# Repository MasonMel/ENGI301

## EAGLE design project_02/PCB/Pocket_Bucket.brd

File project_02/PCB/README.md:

In this project, I implemented my project_01 design into a PCB. This involved creating my own library, schematic, and routing the board layout.

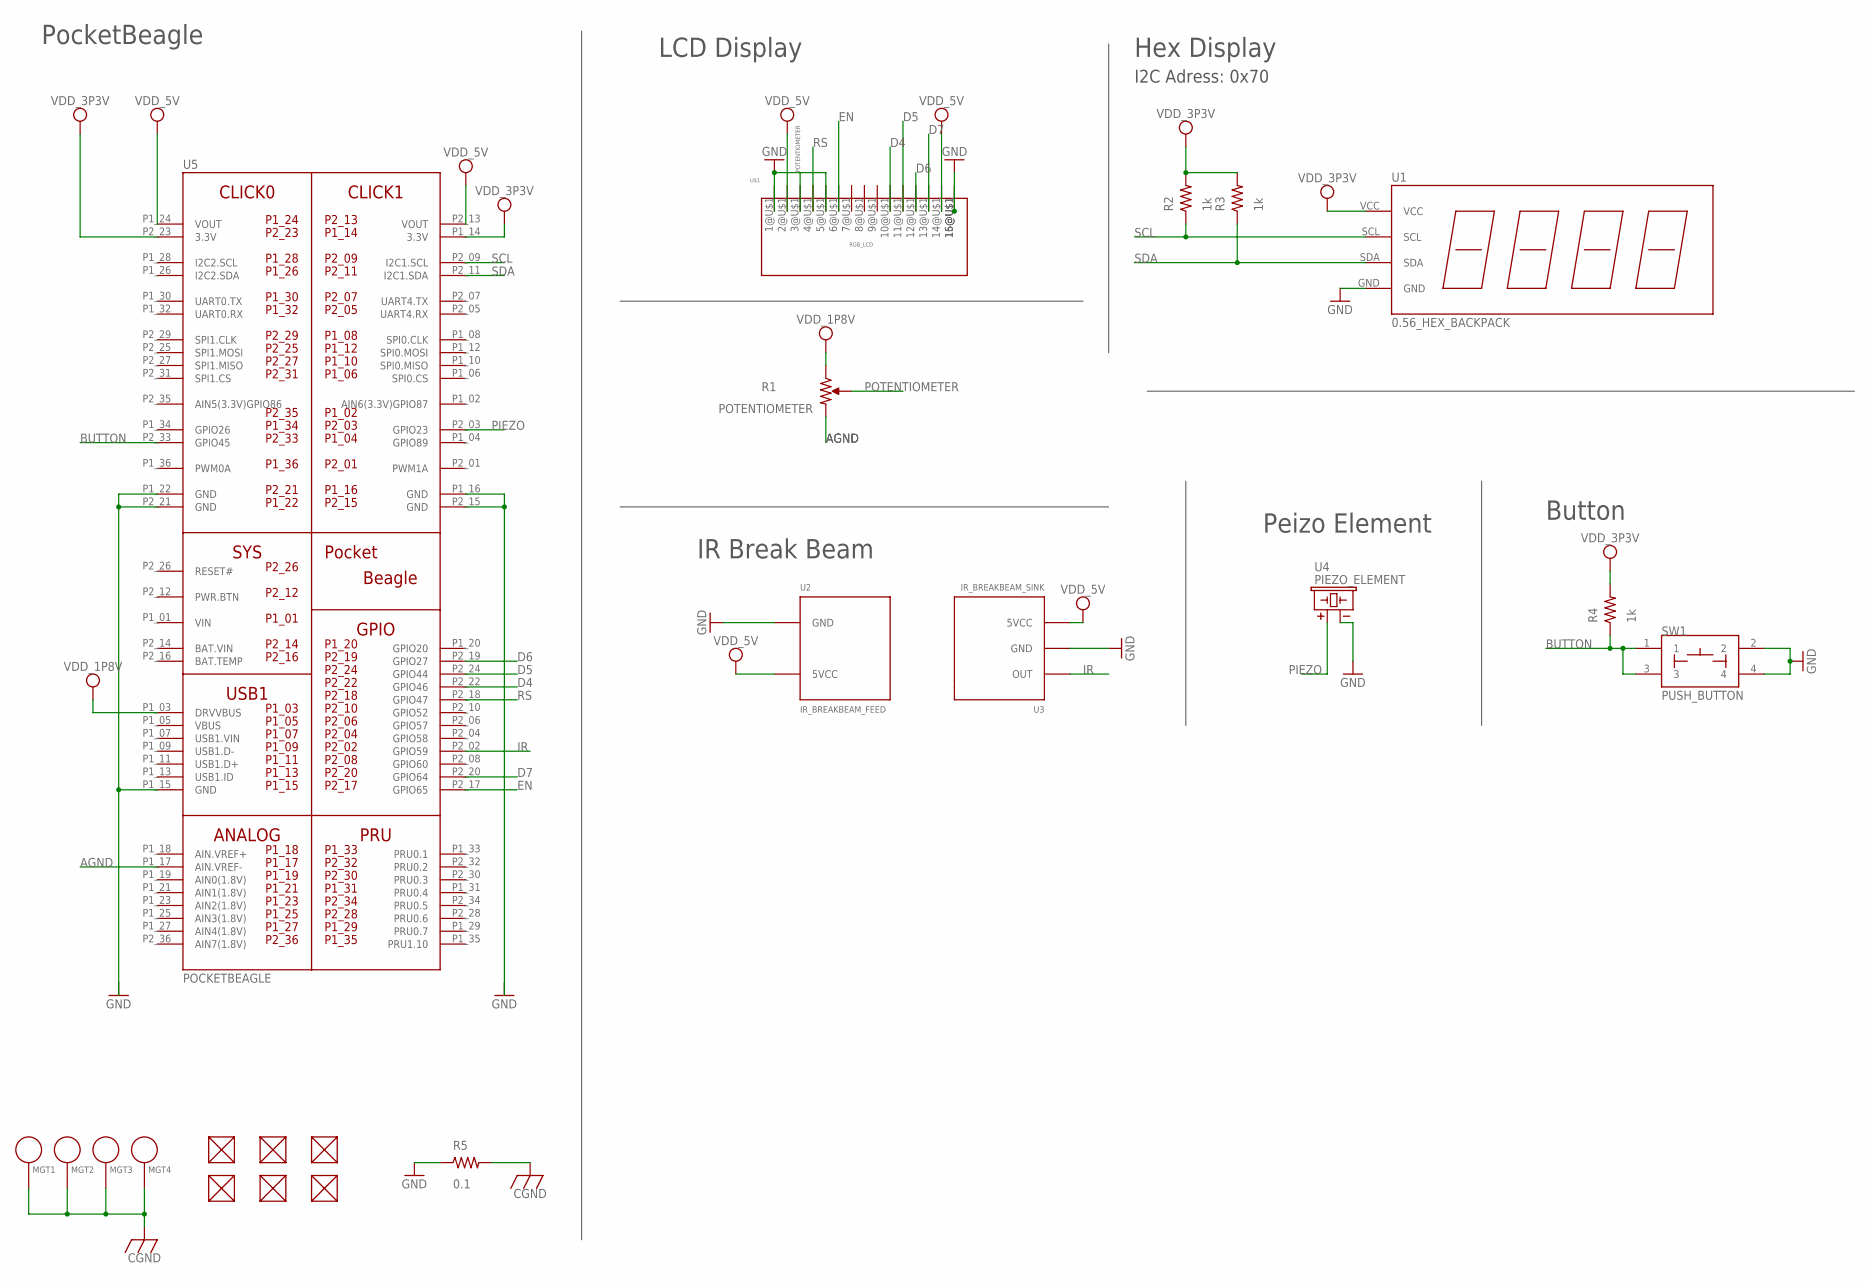
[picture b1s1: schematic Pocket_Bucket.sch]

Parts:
FUD1, FUD2, FUD3, FUD4, FUD5, FUD6: FIDUCIAL; FIDUCIAL_40MIL
MGT1, MGT2, MGT3, MGT4: MOUNTING_HOLE
R1: POTENTIOMETER; POT-PO90S
R2, R3, R4: 1k; R0603
R5: 0.1; R0805
SW1: PUSH_BUTTON; BUTTON_12.5MM
U1: 0.56_HEX_BACKPACK
U2: IR_BREAKBEAM_FEED
U3: IR_BREAKBEAM_SINK
U4: PIEZO_ELEMENT; BUZZER_6.5MM
U5: POCKETBEAGLE
U$1: RGB_LCD; ADAFRUIT_RGB_LCD

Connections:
AGND: R1.CW, U5.P1_15 (GND), U5.P1_17 (AIN.VREF-), U5.P1_22 (GND), U5.P2_21 (GND)
BAT.VIN: U5.P2_14 (BAT.VIN)
BUTTON: R4.1, SW1.1, SW1.3, U5.P2_33 (GPIO45)
CGND: MGT1.P$1, MGT2.P$1, MGT3.P$1, MGT4.P$1, R5.2
D4: U5.P2_22 (GPIO46), U$1.10@U$1 (DB3)
D5: U5.P2_24 (GPIO44), U$1.11@U$1 (DB4)
D6: U5.P2_19 (GPIO27), U$1.12@U$1 (DB5)
D7: U5.P2_20 (GPIO64), U$1.13@U$1 (DB6)
EN: U5.P2_17 (GPIO65), U$1.6@U$1 (E)
GND: R5.1, SW1.2, SW1.4, U1.GND, U2.GND, U3.GND, U4.-, U5.P1_16 (GND), U5.P2_15 (GND), U$1.1@U$1 (VSS), U$1.5@U$1 (RW), U$1.15@U$1 (A), U$1.16@U$1 (K)
IR: U3.OUT, U5.P2_02 (GPIO59)
PIEZO: U4.+, U5.P2_03 (GPIO23)
POTENTIOMETER: R1.S, U$1.3@U$1 (V0)
RS: U5.P2_18 (GPIO47), U$1.4@U$1 (RS)
SCL: R2.1, U1.SCL, U5.P2_09 (I2C1.SCL)
SDA: R3.1, U1.SDA, U5.P2_11 (I2C1.SDA)
VDD_1P8V: R1.CCW, U5.P1_03 (DRVVBUS)
VDD_3P3V: R2.2, R3.2, R4.2, U1.VCC, U5.P1_14 (3.3V), U5.P2_23 (3.3V)
VDD_5V: U2.5VCC, U3.5VCC, U5.P1_24 (VOUT), U5.P2_13 (VOUT), U$1.2@U$1 (VDD), U$1.14@U$1 (DB7)
VIN: U5.P1_01 (VIN)

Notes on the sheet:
PocketBeagle
LCD Display
Hex Display
IR Break Beam
Peizo Element
Button
I2C Adress: 0x70

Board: 2 copper layers, 22 parts (0 on the bottom side), 18 nets, no tracks yet.

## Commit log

2023-11-21 Adding contents necessary to run Pocket Bucket
2023-11-21 Create Project_01
2023-11-21 Move contents to project_01 folder
2023-11-21 Making folder for project_01
2023-12-10 Create Project_02
2023-12-10 Create docs
2023-12-10 Rename ENGI301_project_02.pptx to docs
2023-12-10 Create ppt
2023-12-10 Create read
